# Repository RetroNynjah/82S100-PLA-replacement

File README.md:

# 82S100 CPLD based PLA replacement
This replacement is a remix of [an old design by Mattis Lind](https://github.com/MattisLind/82S100replacement) based on the ATF1502 and compatible PLDs.  
Revision 1 of the board uses the same pinout so my board can be used with MattisLind's C64 PLA code without modification.
Revision 1b is reverted. The parts are on the back side giving the PLA a cleaner look. Because it's inverted, the pinout of the CPLD is different and it needs different code. Grab code for the right PCB!  

## Code
I have made minor adjustments to Mattis's code to enable the CE pin. The CE pin is grounded in all Commodore machines but this makes the PLA match the original better when tested in chip testers that test the CE pin.
The code is written in CUPL. PLD, JED and SVF files are available in the hdl folder for each board revision.
I have created PLA code for the below models
|Model         |Part number |
|:----------    |:----------  |
|C64           |906114-01   |
|CBM-II HP     |906114-05   |
|C16 & Plus/4  |251641-02   |
|CBM 1551      |251641-03   |

## Programming
The CPLD is programmed using JTAG. I'm writing the with svf files using OpenOCD and a FT232H USB breakout board.  
Just be sure to grab the right svf file for your pcb revision.

## Testing
I have custom logic device definitions for Xgpro for the Minipro TL866-II and T48. Those can be used to verify that you have written the correct file and that the PCB is soldered correctly.

## BOM
The part count is low: One ATF1502 CPLD, two 100nF caps (0603) and suitable pin headers.
For rev 1, I prefer flat pins (Arduino stackable headers) or SIL contact strips like [TE 1544210-2](https://www.digikey.se/short/f8hvfqzt) for a number of reason. They give a much lower profile, they stick better to sockets than round machined pins do and they are not as fragile as machined pins. The low profile is ideal for the Plus/4 and the 1551 paddle PLA.  
For rev 1b, machined pins are better as the components are mounted on the back side and the machined headers adds the necessary clearance.  

The CPLD I've been using and recommend is ATF1502ASL-25AU44. It's possible that other varations may work too but it needs to be a 5V part. The 10ns version is causing glitches when used for a C64 PLA.

## Rev 1

## Rev 1b

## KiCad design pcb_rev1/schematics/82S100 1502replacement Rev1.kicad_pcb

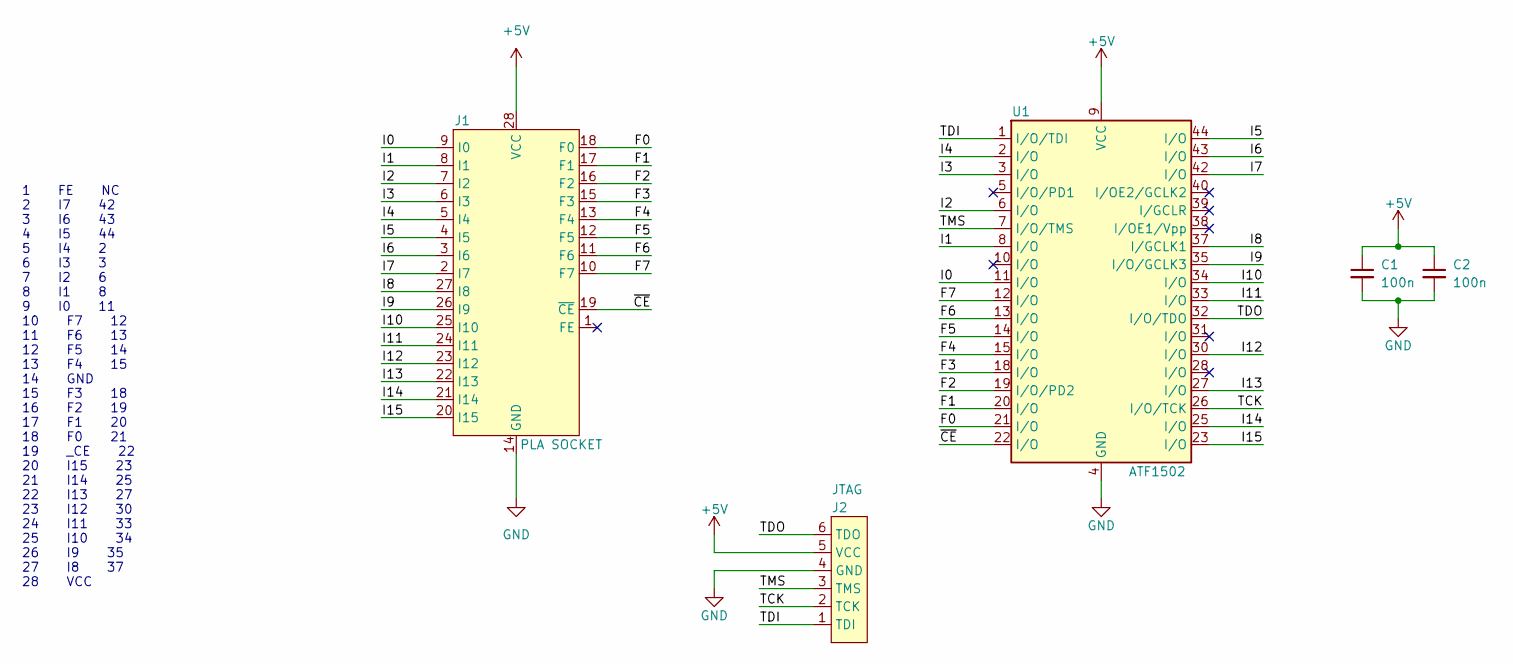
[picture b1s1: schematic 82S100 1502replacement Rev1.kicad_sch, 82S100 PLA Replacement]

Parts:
C1, C2: 100n; C_0603_1608Metric_Pad1.08x0.95mm_HandSolder
J1: PLA SOCKET; DIP-28_W15.24mm_BottomHeadersFlat
J2: JTAG; PinHeader_2x03_P2.54mm_Vertical
U1: ATF1502; TQFP-44_10x10mm_P0.8mm

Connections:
+5V: C1.1, C2.1, J1.28 (VCC), J2.5 (VCC), U1.9 (VCC), U1.17 (VCC), U1.29 (VCC), U1.41 (VCC)
/F0: J1.18 (F0), U1.21 (I/O)
/F1: J1.17 (F1), U1.20 (I/O)
/F2: J1.16 (F2), U1.19 (I/O/PD2)
/F3: J1.15 (F3), U1.18 (I/O)
/F4: J1.13 (F4), U1.15 (I/O)
/F5: J1.12 (F5), U1.14 (I/O)
/F6: J1.11 (F6), U1.13 (I/O)
/F7: J1.10 (F7), U1.12 (I/O)
/I0: J1.9 (I0), U1.11 (I/O)
/I1: J1.8 (I1), U1.8 (I/O)
/I2: J1.7 (I2), U1.6 (I/O)
/I3: J1.6 (I3), U1.3 (I/O)
/I4: J1.5 (I4), U1.2 (I/O)
/I5: J1.4 (I5), U1.44 (I/O)
/I6: J1.3 (I6), U1.43 (I/O)
/I7: J1.2 (I7), U1.42 (I/O)
/I8: J1.27 (I8), U1.37 (I/GCLK1)
/I9: J1.26 (I9), U1.35 (I/O/GCLK3)
/I10: J1.25 (I10), U1.34 (I/O)
/I11: J1.24 (I11), U1.33 (I/O)
/I12: J1.23 (I12), U1.30 (I/O)
/I13: J1.22 (I13), U1.27 (I/O)
/I14: J1.21 (I14), U1.25 (I/O)
/I15: J1.20 (I15), U1.23 (I/O)
/TCK: J2.2 (TCK), U1.26 (I/O/TCK)
/TDI: J2.1 (TDI), U1.1 (I/O/TDI)
/TDO: J2.6 (TDO), U1.32 (I/O/TDO)
/TMS: J2.3 (TMS), U1.7 (I/O/TMS)
/~CE: J1.19 (~CE), U1.22 (I/O)
GND: C1.2, C2.2, J1.14 (GND), J2.4 (GND), U1.4 (GND), U1.16 (GND), U1.24 (GND), U1.36 (GND)

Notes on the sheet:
1 FE NC 2 I7 42 3 I6 43 4 I5 44 5 I4 2 6 I3 3 7 I2 6 8 I1 8 9 I0 11 10 F7 12 11 F6 13 12 F5 14 13 F4 15 14 GND 15 F3 18 16 F2 19 17 F1 20 18 F0 21 19 _CE 22 20 I15 23 21 I14 25 22 I13 27 23 I12 30 24 I11 33 25 I10 34 26 I9 35 27 I8 37 28 VCC

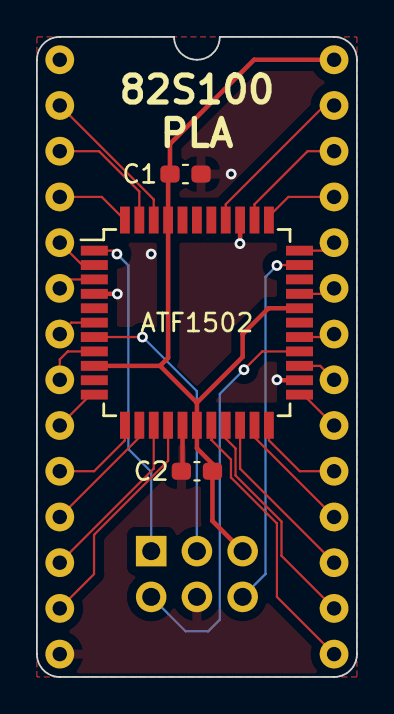
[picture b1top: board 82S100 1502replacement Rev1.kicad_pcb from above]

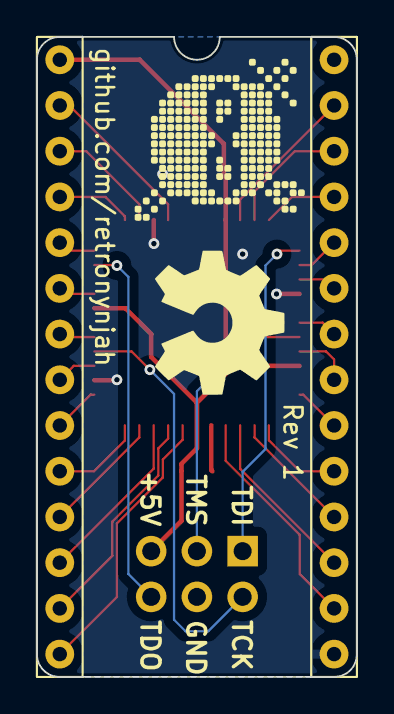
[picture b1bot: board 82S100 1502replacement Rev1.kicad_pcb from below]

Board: 2 copper layers, 17.8 x 35.6 mm, 7 parts (3 on the bottom side), 31 nets.

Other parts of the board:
Logo: retroninja; LOGO
Logo2: OSHW; LOGO

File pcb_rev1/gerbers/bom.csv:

Designator,Footprint,Quantity,Value,LCSC Part #
"C1, C2",0603,2,100n,
J1,DIP-28_W15.24mm_BottomHeadersFlat,1,PLA SOCKET,
J2,PinHeader_2x03_P2.54mm_Vertical,1,JTAG,
U1,TQFP-44_10x10mm_P0.8mm,1,ATF1502,

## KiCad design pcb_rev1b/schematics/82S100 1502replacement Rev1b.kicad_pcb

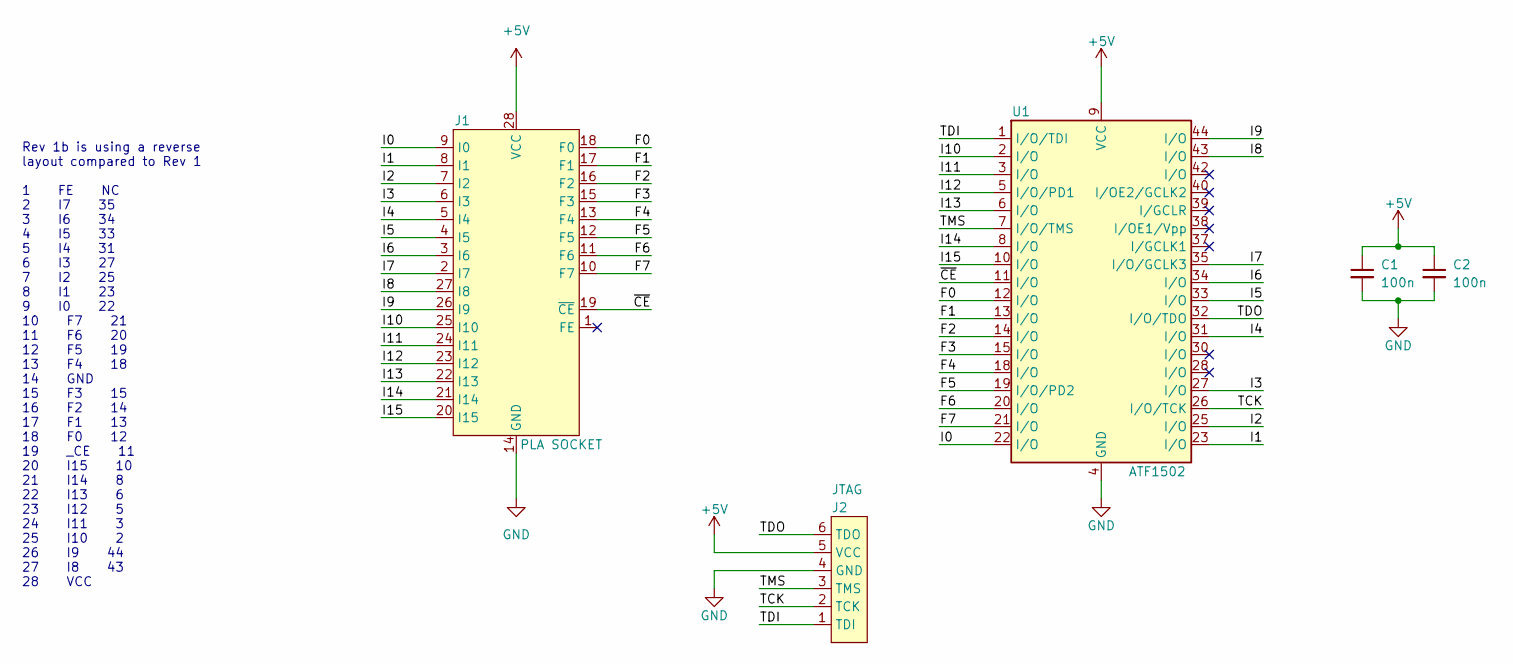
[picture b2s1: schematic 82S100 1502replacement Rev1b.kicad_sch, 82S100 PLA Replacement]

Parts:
C1, C2: 100n; C_0603_1608Metric_Pad1.08x0.95mm_HandSolder
J1: PLA SOCKET; DIP-28_W15.24mm_BottomHeadersFlat
J2: JTAG; PinHeader_2x03_P2.54mm_Vertical
U1: ATF1502; TQFP-44_10x10mm_P0.8mm

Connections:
+5V: C1.1, C2.1, J1.28 (VCC), J2.5 (VCC), U1.9 (VCC), U1.17 (VCC), U1.29 (VCC), U1.41 (VCC)
/F0: J1.18 (F0), U1.12 (I/O)
/F1: J1.17 (F1), U1.13 (I/O)
/F2: J1.16 (F2), U1.14 (I/O)
/F3: J1.15 (F3), U1.15 (I/O)
/F4: J1.13 (F4), U1.18 (I/O)
/F5: J1.12 (F5), U1.19 (I/O/PD2)
/F6: J1.11 (F6), U1.20 (I/O)
/F7: J1.10 (F7), U1.21 (I/O)
/I0: J1.9 (I0), U1.22 (I/O)
/I1: J1.8 (I1), U1.23 (I/O)
/I2: J1.7 (I2), U1.25 (I/O)
/I3: J1.6 (I3), U1.27 (I/O)
/I4: J1.5 (I4), U1.31 (I/O)
/I5: J1.4 (I5), U1.33 (I/O)
/I6: J1.3 (I6), U1.34 (I/O)
/I7: J1.2 (I7), U1.35 (I/O/GCLK3)
/I8: J1.27 (I8), U1.43 (I/O)
/I9: J1.26 (I9), U1.44 (I/O)
/I10: J1.25 (I10), U1.2 (I/O)
/I11: J1.24 (I11), U1.3 (I/O)
/I12: J1.23 (I12), U1.5 (I/O/PD1)
/I13: J1.22 (I13), U1.6 (I/O)
/I14: J1.21 (I14), U1.8 (I/O)
/I15: J1.20 (I15), U1.10 (I/O)
/TCK: J2.2 (TCK), U1.26 (I/O/TCK)
/TDI: J2.1 (TDI), U1.1 (I/O/TDI)
/TDO: J2.6 (TDO), U1.32 (I/O/TDO)
/TMS: J2.3 (TMS), U1.7 (I/O/TMS)
/~CE: J1.19 (~CE), U1.11 (I/O)
GND: C1.2, C2.2, J1.14 (GND), J2.4 (GND), U1.4 (GND), U1.16 (GND), U1.24 (GND), U1.36 (GND)

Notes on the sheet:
Rev 1b is using a reverse layout compared to Rev 1 1 FE NC 2 I7 35 3 I6 34 4 I5 33 5 I4 31 6 I3 27 7 I2 25 8 I1 23 9 I0 22 10 F7 21 11 F6 20 12 F5 19 13 F4 18 14 GND 15 F3 15 16 F2 14 17 F1 13 18 F0 12 19 _CE 11 20 I15 10 21 I14 8 22 I13 6 23 I12 5 24 I11 3 25 I10 2 26 I9 44 27 I8 43 28 VCC

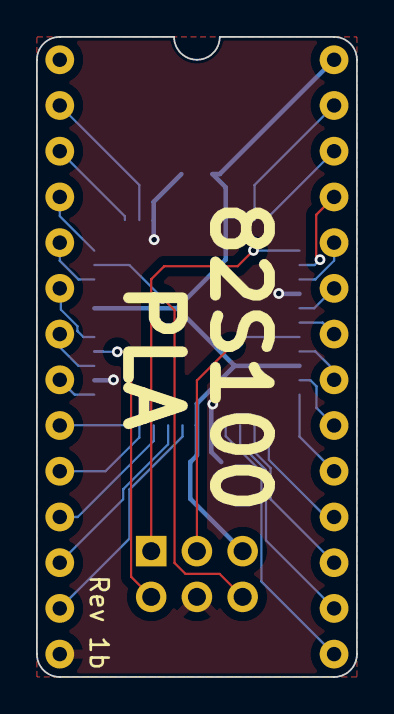
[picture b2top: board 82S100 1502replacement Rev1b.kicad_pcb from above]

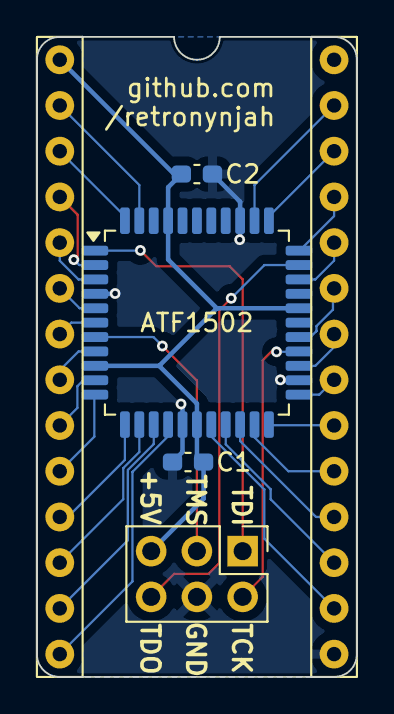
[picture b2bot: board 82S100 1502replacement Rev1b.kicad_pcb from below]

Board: 2 copper layers, 17.8 x 35.6 mm, 5 parts (4 on the bottom side), 31 nets.

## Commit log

2024-11-30 Initial upload
    PCB rev 1
2025-02-15 Update README.md
    Added information about CPLD speeds.
2026-06-22 Revision 1b
    Added:
    PCB revision 1b,
    906114-05 CBM-II PLA,
    Changed:
    Minor updates to most CUPL code,
    Reorganized file structure,
2026-06-22 Added Xgpro definitions
2026-06-22 Updated README
    Updated the README to clarify CE pin adjustments and CPLD recommendations. Added testing section for custom logic device definitions.
2026-06-23 Fix typo in README regarding CPLD version
